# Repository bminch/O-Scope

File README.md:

# O-Scope
This repository contains the PCB design files, firmware, and software for the O-Scope, which is a low-cost (i.e., a cut-tape BoM cost of about $30 
as of fall 2020) two-channel oscilloscope / single-channel waveform generator up to a bandwidth of 200 kHz that fits into a solderless breadboard.  The oscilloscope's vertical resolution is 12 bits and each channel is sampled at 4 MS/s.  Each channel has a sample buffer of 1,500 points.  The 
oscilloscope probes are differential and have an equivalent input impedance of 1 MΩ || 15 pF with two input voltage ranges: ±10V and ±2V.  The 
waveform generator is capable of producing DC, sinusoidal, square, and triangle waves with an adjustable offset in the range of 0 - 5V. For an overview 
and demonstration of the O-Scope, see https://youtu.be/0cz0oYtfNsY.

I designed this instrument during the summer of 2020 based on a prior prototype, which I had made during the summers of 2016 and 2017, in order to support 
a remote / hybrid offering of ENGR 1125: Introduction to Sensors, Instrumentation, and Measurement at Olin College during the spring of 2021 in the midst 
of the COVID-19 pandemic.  During October and November 2020, I hand assembled and calibrated 90 O-Scopes at home, as shown in https://youtu.be/zYawotioLMc.  We used these instruments successfully during the spring 2021 and spring 2022 offerings of the course at Olin.

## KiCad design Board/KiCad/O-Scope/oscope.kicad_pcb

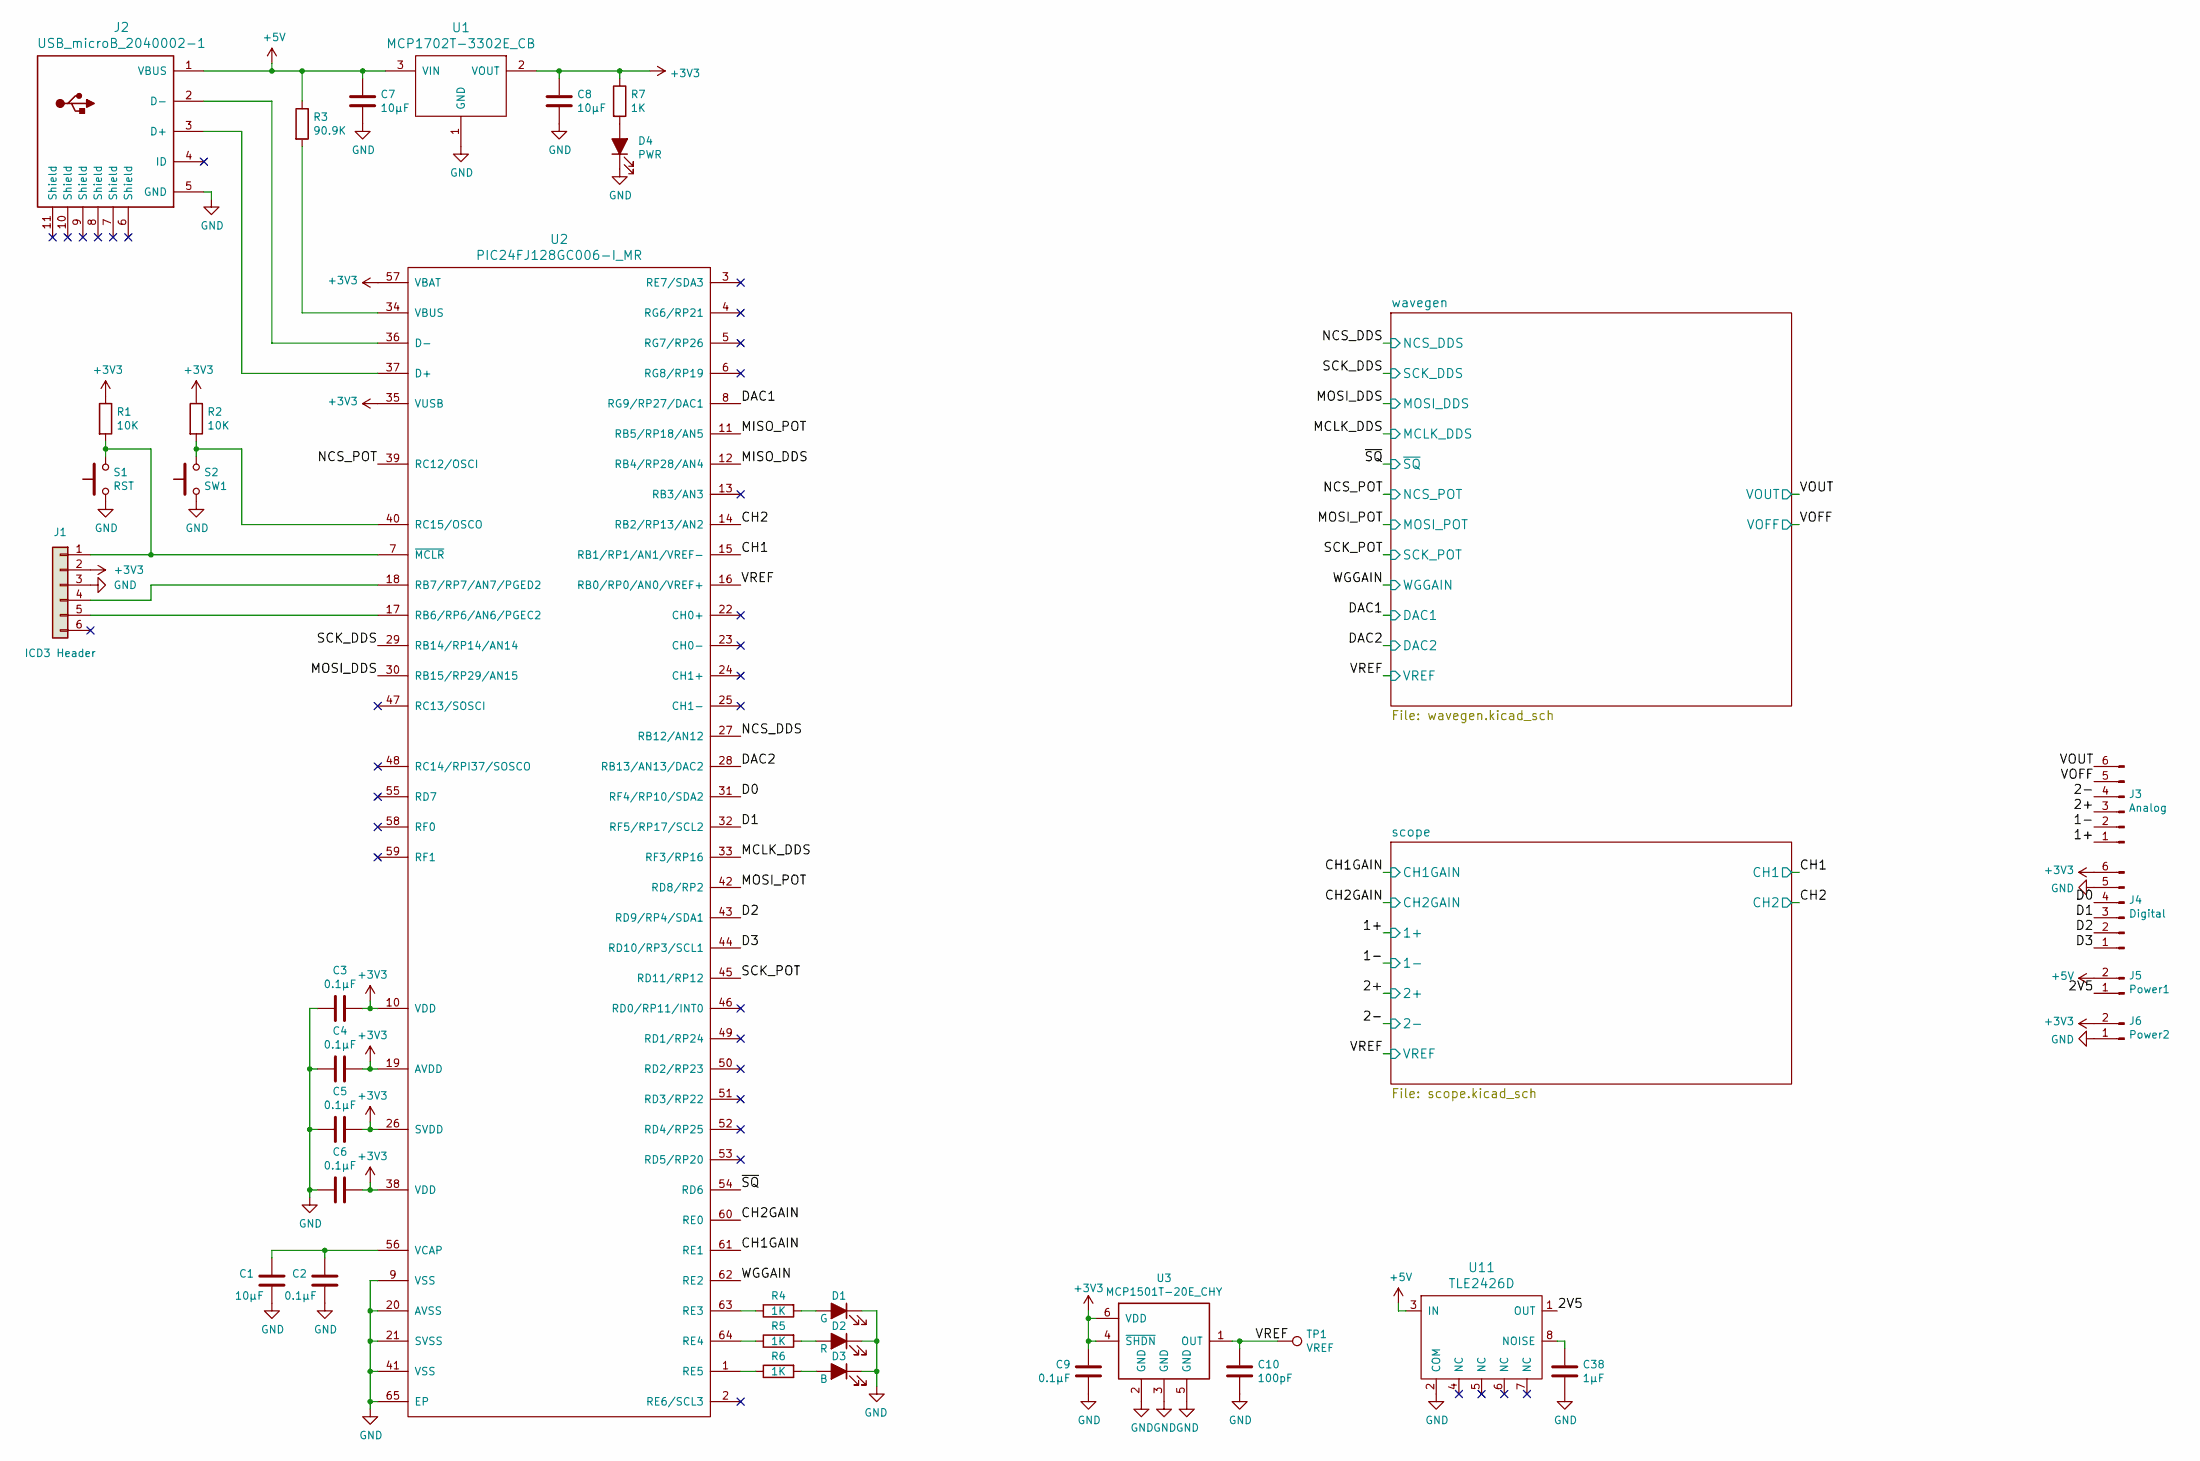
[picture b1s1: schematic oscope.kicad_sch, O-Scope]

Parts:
C1, C7, C8: 10µF; C_0805_2012Metric
C2, C3, C4, C5, C6, C9: 0.1µF; C_0603_1608Metric
C10: 100pF; C_0603_1608Metric
C38: 1µF; C_0603_1608Metric
D1: G; LED_0805_2012Metric
D2: R; LED_0805_2012Metric
D3: B; LED_0805_2012Metric
D4: PWR; LED_0805_2012Metric
J1: ICD3 Header; ICD3_header
J2: USB_microB_2040002-1
J3: Analog; PinHeader_1x06_P2.54mm_Vertical
J4: Digital; PinHeader_1x06_P2.54mm_Vertical
J5: Power1; PinHeader_1x02_P2.54mm_Vertical
J6: Power2; PinHeader_1x02_P2.54mm_Vertical
R1, R2: 10K; R_0603_1608Metric
R3: 90.9K; R_0603_1608Metric
R4, R5, R6, R7: 1K; R_0603_1608Metric
S1: RST; SW_SPST_B3U-1000P
S2: SW1; SW_SPST_B3U-1000P
TP1: VREF; 60mil_testpoint
U1: MCP1702T-3302E_CB; SOT-23
U2: PIC24FJ128GC006-I_MR; pic24fj128gc006
U3: MCP1501T-20E_CHY; SOT-23-6
U11: TLE2426D; SO-8_3.9x4.9mm_P1.27mm

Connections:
+3V3: C3.2, C4.2, C5.2, C6.2, C8.1, C9.1, J1.2, J4.6, J6.2, R1.1, R2.1, R7.1, U1.2 (VOUT), U2.10 (VDD), U2.19 (AVDD), U2.26 (SVDD), U2.35 (VUSB), U2.38 (VDD), U2.57 (VBAT), U3.4 (~SHDN), U3.6 (VDD); also elsewhere on the board
+5V: C7.1, J2.1 (VBUS), J5.2, R3.1, U1.3 (VIN), U11.3 (IN); also elsewhere on the board
/1+: J3.1; also elsewhere on the board
/1-: J3.2; also elsewhere on the board
/2+: J3.3; also elsewhere on the board
/2-: J3.4; also elsewhere on the board
/2V5: J5.1, U11.1 (OUT)
/CH1: U2.15 (RB1/RP1/AN1/VREF-); also elsewhere on the board
/CH1GAIN: U2.61 (RE1); also elsewhere on the board
/CH2: U2.14 (RB2/RP13/AN2); also elsewhere on the board
/CH2GAIN: U2.60 (RE0); also elsewhere on the board
/D0: J4.4, U2.31 (RF4/RP10/SDA2)
/D1: J4.3, U2.32 (RF5/RP17/SCL2)
/D2: J4.2, U2.43 (RD9/RP4/SDA1)
/D3: J4.1, U2.44 (RD10/RP3/SCL1)
/DAC1: U2.8 (RG9/RP27/DAC1); also elsewhere on the board
/DAC2: U2.28 (RB13/AN13/DAC2); also elsewhere on the board
/MCLK_DDS: U2.33 (RF3/RP16); also elsewhere on the board
/MISO_DDS: U2.12 (RB4/RP28/AN4)
/MISO_POT: U2.11 (RB5/RP18/AN5)
/MOSI_DDS: U2.30 (RB15/RP29/AN15); also elsewhere on the board
/MOSI_POT: U2.42 (RD8/RP2); also elsewhere on the board
/NCS_DDS: U2.27 (RB12/AN12); also elsewhere on the board
/NCS_POT: U2.39 (RC12/OSCI); also elsewhere on the board
/SCK_DDS: U2.29 (RB14/RP14/AN14); also elsewhere on the board
/SCK_POT: U2.45 (RD11/RP12); also elsewhere on the board
/VOFF: J3.5; also elsewhere on the board
/VOUT: J3.6; also elsewhere on the board
/VREF: C10.1, TP1.1, U2.16 (RB0/RP0/AN0/VREF+), U3.1 (OUT); also elsewhere on the board
/WGGAIN: U2.62 (RE2); also elsewhere on the board
/~SQ: U2.54 (RD6); also elsewhere on the board
GND: C1.1, C2.1, C3.1, C4.1, C5.1, C6.1, C7.2, C8.2, C9.2, C10.2, C38.2, D1.1 (K), D2.1 (K), D3.1 (K), D4.1 (K), J1.3, J2.5 (GND), J4.5, J6.1, S1.1, S2.1, U1.1 (GND), U2.9 (VSS), U2.20 (AVSS), U2.21 (SVSS), U2.41 (VSS), U2.65 (EP), U3.2 (GND), U3.3 (GND), U3.5 (GND), U11.2 (COM); also elsewhere on the board
unnamed: C1.2, C2.2, U2.56 (VCAP)
unnamed: C38.1, U11.8 (NOISE)
unnamed: D1.2 (A), R4.2
unnamed: D2.2 (A), R5.2
unnamed: D3.2 (A), R6.2
unnamed: D4.2 (A), R7.2
unnamed: J1.1, R1.2, S1.2, U2.7 (~MCLR)
unnamed: J1.4, U2.18 (RB7/RP7/AN7/PGED2)
unnamed: J1.5, U2.17 (RB6/RP6/AN6/PGEC2)
unnamed: J2.2 (D-), U2.36 (D-)
unnamed: J2.3 (D+), U2.37 (D+)
unnamed: R2.2, S2.2, U2.40 (RC15/OSCO)
unnamed: R3.2, U2.34 (VBUS)
unnamed: R4.1, U2.63 (RE3)
unnamed: R5.1, U2.64 (RE4)
unnamed: R6.1, U2.1 (RE5)

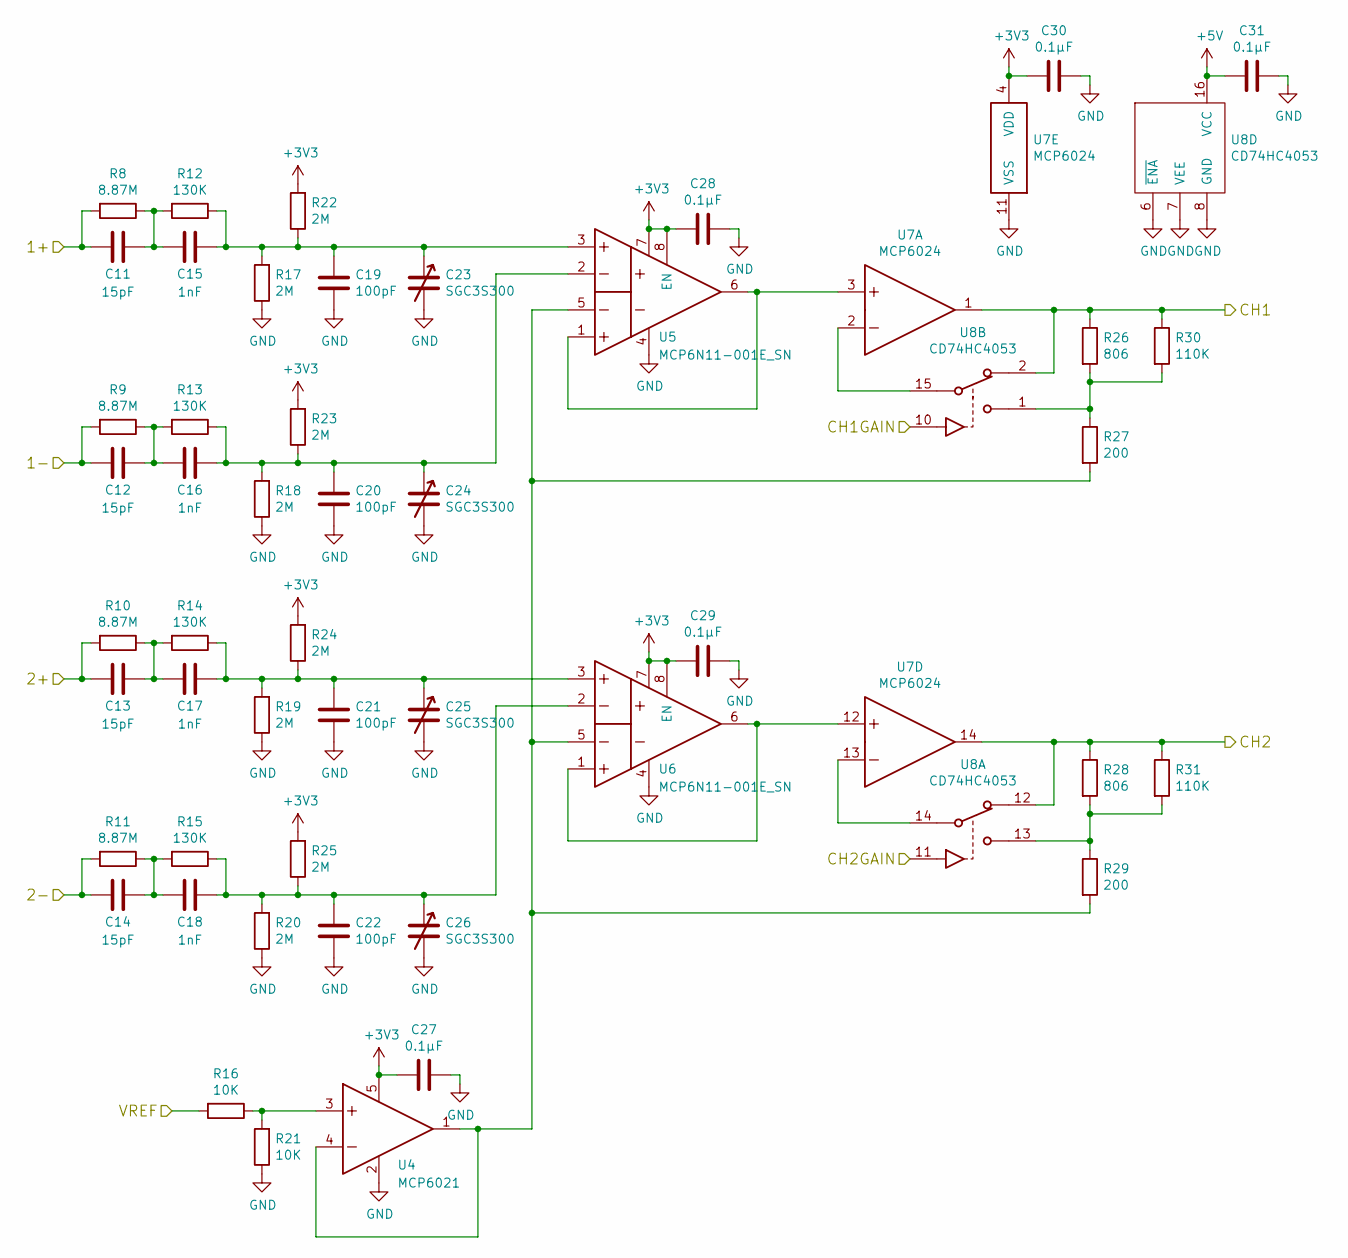
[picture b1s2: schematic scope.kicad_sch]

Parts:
C11, C12, C13, C14: 15pF; C_0603_1608Metric
C15, C16, C17, C18: 1nF; C_0603_1608Metric
C19, C20, C21, C22: 100pF; C_0603_1608Metric
C23, C24, C25, C26: SGC3S300; C_Trimmer_Sprague-Goodman_SGC3
C27, C28, C29, C30, C31: 0.1µF; C_0603_1608Metric
R8, R9, R10, R11: 8.87M; R_0805_2012Metric
R12, R13, R14, R15: 130K; R_0603_1608Metric
R16, R21: 10K; R_0603_1608Metric
R17, R18, R19, R20, R22, R23, R24, R25: 2M; R_0603_1608Metric
R26, R28: 806; R_0603_1608Metric
R27, R29: 200; R_0603_1608Metric
R30, R31: 110K; R_0603_1608Metric
U4: MCP6021; SOT-23-5
U5, U6: MCP6N11-001E_SN; SOIC-8_3.9x4.9mm_P1.27mm
U7: MCP6024; TSSOP-14_4.4x5mm_P0.65mm
U8: CD74HC4053; TSSOP-16_4.4x5mm_P0.65mm

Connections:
+3V3: C27.2, C28.2, C29.2, C30.2, R22.2, R23.2, R24.2, R25.2, U4.5, U5.7, U5.8 (EN), U6.7, U6.8 (EN), U7.4 (VDD); also elsewhere on the board
+5V: C31.2, U8.16 (VCC); also elsewhere on the board
/1+: C11.1, R8.2; also elsewhere on the board
/1-: C12.1, R9.2; also elsewhere on the board
/2+: C13.1, R10.2; also elsewhere on the board
/2-: C14.1, R11.2; also elsewhere on the board
/CH1: R26.1, R30.1, U7.1, U8.2; also elsewhere on the board
/CH1GAIN: U8.10; also elsewhere on the board
/CH2: R28.1, R31.1, U7.14, U8.12; also elsewhere on the board
/CH2GAIN: U8.11; also elsewhere on the board
/VREF: R16.2; also elsewhere on the board
GND: C19.2, C20.2, C21.2, C22.2, C23.2, C24.2, C25.2, C26.2, C27.1, C28.1, C29.1, C30.1, C31.1, R17.1, R18.1, R19.1, R20.1, R21.1, U4.2, U5.4, U6.4, U7.11 (VSS), U8.6 (~ENA), U8.7 (VEE), U8.8 (GND); also elsewhere on the board
unnamed: C11.2, C15.1, R8.1, R12.2
unnamed: C12.2, C16.1, R9.1, R13.2
unnamed: C13.2, C17.1, R10.1, R14.2
unnamed: C14.2, C18.1, R11.1, R15.2
unnamed: C15.2, C19.1, C23.1, R12.1, R17.2, R22.1, U5.3
unnamed: C16.2, C20.1, C24.1, R13.1, R18.2, R23.1, U5.2
unnamed: C17.2, C21.1, C25.1, R14.1, R19.2, R24.1, U6.3
unnamed: C18.2, C22.1, C26.1, R15.1, R20.2, R25.1, U6.2
unnamed: R16.1, R21.2, U4.3
unnamed: R26.2, R27.1, R30.2, U8.1
unnamed: R27.2, R29.2, U4.1, U4.4, U5.5, U6.5
unnamed: R28.2, R29.1, R31.2, U8.13
unnamed: U5.1, U5.6, U7.3
unnamed: U6.1, U6.6, U7.12
unnamed: U7.2, U8.15
unnamed: U7.13, U8.14

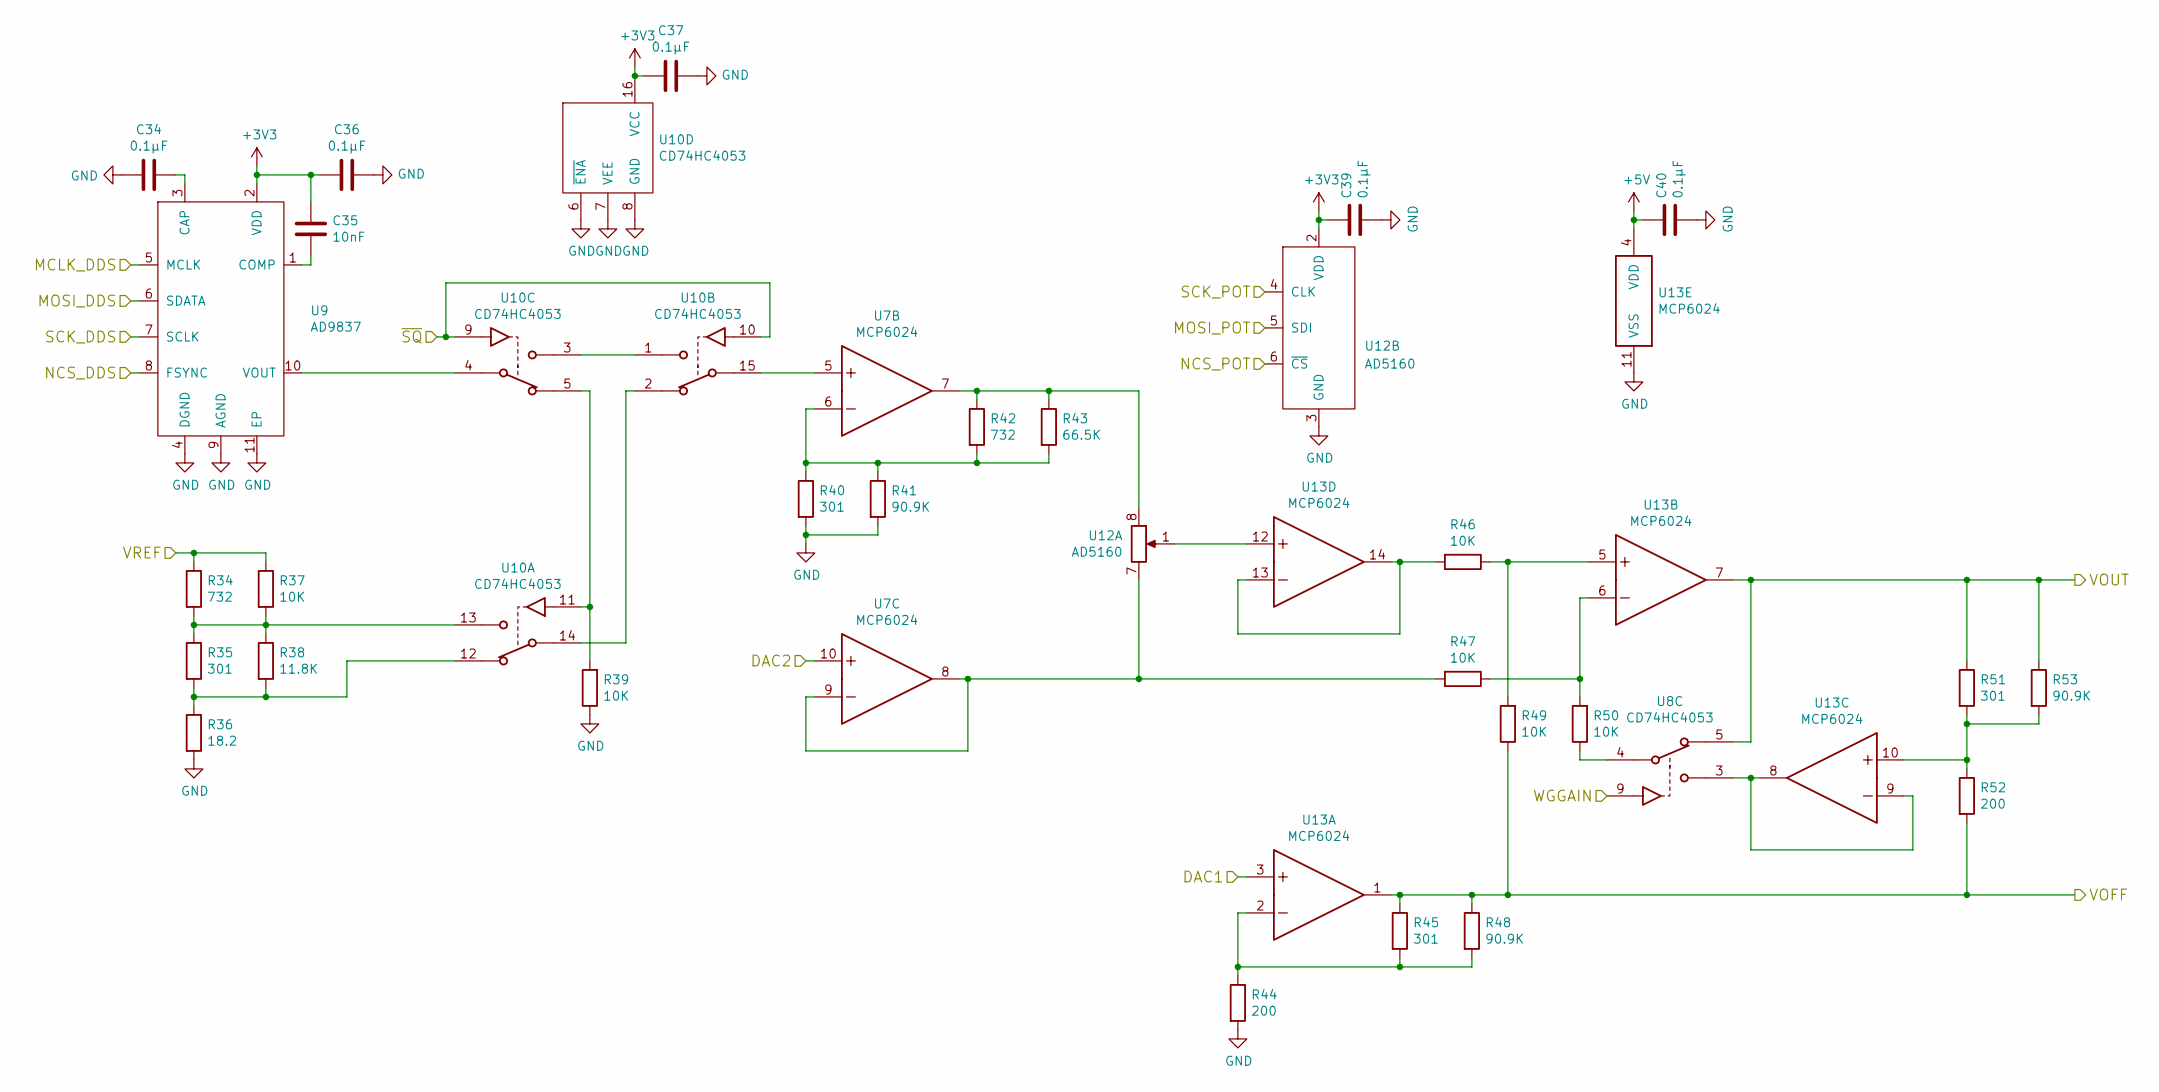
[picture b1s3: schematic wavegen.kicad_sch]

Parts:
C34, C36, C37, C39, C40: 0.1µF; C_0603_1608Metric
C35: 10nF; C_0603_1608Metric
R34, R42: 732; R_0603_1608Metric
R35, R40, R45, R51: 301; R_0603_1608Metric
R36: 18.2; R_0603_1608Metric
R37, R39, R46, R47, R49, R50: 10K; R_0603_1608Metric
R38: 11.8K; R_0603_1608Metric
R41, R48, R53: 90.9K; R_0603_1608Metric
R43: 66.5K; R_0603_1608Metric
R44, R52: 200; R_0603_1608Metric
U7, U13: MCP6024; TSSOP-14_4.4x5mm_P0.65mm
U8, U10: CD74HC4053; TSSOP-16_4.4x5mm_P0.65mm
U9: AD9837
U12: AD5160; TSOT-23-8

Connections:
+3V3: C35.1, C36.2, C37.2, C39.1, U9.2 (VDD), U10.16 (VCC), U12.2 (VDD); also elsewhere on the board
+5V: C40.1, U13.4 (VDD); also elsewhere on the board
/DAC1: U13.3; also elsewhere on the board
/DAC2: U7.10; also elsewhere on the board
/MCLK_DDS: U9.5 (MCLK); also elsewhere on the board
/MOSI_DDS: U9.6 (SDATA); also elsewhere on the board
/MOSI_POT: U12.5 (SDI); also elsewhere on the board
/NCS_DDS: U9.8 (FSYNC); also elsewhere on the board
/NCS_POT: U12.6 (~CS); also elsewhere on the board
/SCK_DDS: U9.7 (SCLK); also elsewhere on the board
/SCK_POT: U12.4 (CLK); also elsewhere on the board
/VOFF: R45.1, R48.1, R49.1, R52.2, U13.1; also elsewhere on the board
/VOUT: R51.1, R53.1, U8.5, U13.7; also elsewhere on the board
/VREF: R34.1, R37.1; also elsewhere on the board
/WGGAIN: U8.9; also elsewhere on the board
/~SQ: U10.9, U10.10; also elsewhere on the board
GND: C34.2, C36.1, C37.1, C39.2, C40.2, R36.2, R39.1, R40.2, R41.2, R44.2, U9.4 (DGND), U9.9 (AGND), U9.11 (EP), U10.6 (~ENA), U10.7 (VEE), U10.8 (GND), U12.3 (GND), U13.11 (VSS); also elsewhere on the board
unnamed: C34.1, U9.3 (CAP)
unnamed: C35.2, U9.1 (COMP)
unnamed: R34.2, R35.1, R37.2, R38.1, U10.13
unnamed: R35.2, R36.1, R38.2, U10.12
unnamed: R39.2, U10.5, U10.11
unnamed: R40.1, R41.1, R42.2, R43.2, U7.6
unnamed: R42.1, R43.1, U7.7, U12.8
unnamed: R44.1, R45.2, R48.2, U13.2
unnamed: R46.1, R49.2, U13.5
unnamed: R46.2, U13.13, U13.14
unnamed: R47.1, R50.2, U13.6
unnamed: R47.2, U7.8, U7.9, U12.7
unnamed: R50.1, U8.4
unnamed: R51.2, R52.1, R53.2, U13.10
unnamed: U10.1, U10.3
unnamed: U9.10 (VOUT), U10.4
unnamed: U10.2, U10.14
unnamed: U7.5, U10.15
unnamed: U12.1, U13.12
unnamed: U8.3, U13.8, U13.9

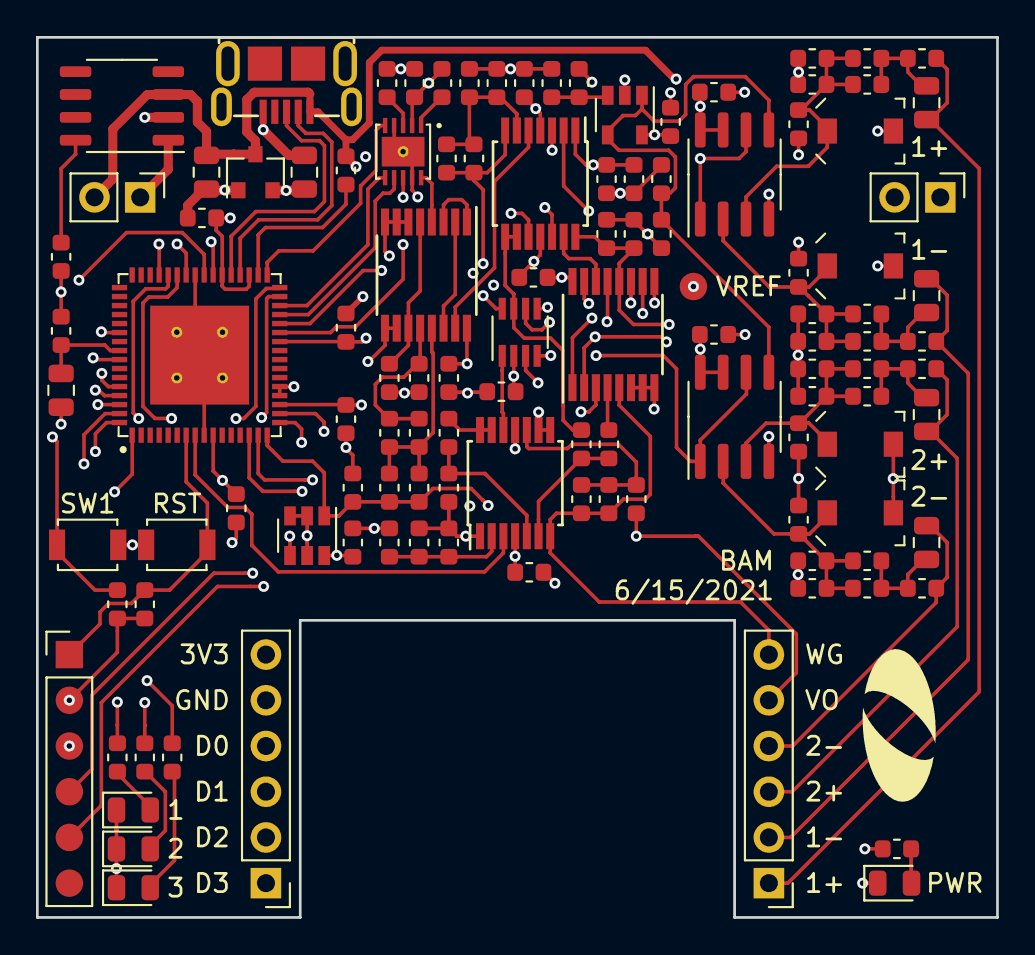
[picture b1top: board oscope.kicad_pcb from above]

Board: 4 copper layers, 53.3 x 48.9 mm, 117 parts (1 on the bottom side), 82 nets.

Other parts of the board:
OlinLogoLg1: G***; OlinLogoLg1
OlinLogoTruncated: G***; OlinLogoTruncated

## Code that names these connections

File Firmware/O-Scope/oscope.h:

#ifndef _OSCOPE_H_
#define _OSCOPE_H_

#include "pic24fj.h"
#include "common.h"
#include <stdint.h>

// LED pin definitions
#define LED1                LATEbits.LATE3
#define LED2                LATEbits.LATE4
#define LED3                LATEbits.LATE5

#define LED1_DIR            TRISEbits.TRISE3
#define LED2_DIR            TRISEbits.TRISE4
#define LED3_DIR            TRISEbits.TRISE5

// Tactile switch pin definitions
#define SW1                 PORTCbits.RC15

#define SW1_DIR             TRISCbits.TRISC15

// Digital header pin definitions
#define D0                  PORTFbits.RF4
#define D1                  PORTFbits.RF5
#define D2                  PORTDbits.RD9
#define D3                  PORTDbits.RD10

#define D0_DIR              TRISFbits.TRISF4
#define D1_DIR              TRISFbits.TRISF5
#define D2_DIR              TRISDbits.TRISD9
#define D3_DIR              TRISDbits.TRISD10

#define D0_LAT              LATFbits.LATF4
#define D1_LAT              LATFbits.LATF5
#define D2_LAT              LATDbits.LATD9
#define D3_LAT              LATDbits.LATD10

#define D0_RP               10
#define D1_RP               17
#define D2_RP               4
#define D3_RP               3

#define D0_OD               ODCFbits.ODF4
#define D1_OD               ODCFbits.ODF5
#define D2_OD               ODCDbits.ODD9
#define D3_OD               ODCDbits.ODD10

#define D0_PU               CNPU2bits.CN17PUE
#define D1_PU               CNPU2bits.CN18PUE
#define D2_PU               CNPU4bits.CN54PUE
#define D3_PU               CNPU4bits.CN55PUE

#define D0_PD               CNPD2bits.CN17PDE
#define D1_PD               CNPD2bits.CN18PDE
#define D2_PD               CNPD4bits.CN54PDE
#define D3_PD               CNPD4bits.CN55PDE

// AD9837 DDS interface pin defintions
#define nCS_DDS             LATBbits.LATB12
#define SCK_DDS             PORTBbits.RB14
#define MOSI_DDS            PORTBbits.RB15
#define MISO_DDS            PORTBbits.RB4
#define MCLK_DDS            PORTFbits.RF3

#define nCS_DDS_DIR         TRISBbits.TRISB12
#define SCK_DDS_DIR         TRISBbits.TRISB14
#define MOSI_DDS_DIR        TRISBbits.TRISB15
#define MISO_DDS_DIR        TRISBbits.TRISB4
#define MCLK_DDS_DIR        TRISFbits.TRISF3

#define SCK_DDS_RP          14
#define MOSI_DDS_RP         29
#define MISO_DDS_RP         28
#define MCLK_DDS_RP         16

// AD5160 digital potentiometer interface pin definitions
#define nCS_POT             LATCbits.LATC12
#define SCK_POT             PORTDbits.RD11
#define MOSI_POT            PORTDbits.RD8
#define MISO_POT            PORTBbits.RB5

#define nCS_POT_DIR         TRISCbits.TRISC12
#define SCK_POT_DIR         TRISDbits.TRISD11
#define MOSI_POT_DIR        TRISDbits.TRISD8
#define MISO_POT_DIR        TRISBbits.TRISB5

#define SCK_POT_RP          12
#define MOSI_POT_RP         2
#define MISO_POT_RP         18

// Wavegen mode pin defitions
#define nSQUARE             LATDbits.LATD6
#define WG_GAIN             LATEbits.LATE2

#define nSQUARE_DIR         TRISDbits.TRISD6
#define WG_GAIN_DIR         TRISEbits.TRISE2

// Scope channel gain pin definitions
#define CH1_GAIN            LATEbits.LATE1
#define CH2_GAIN            LATEbits.LATE0

#define CH1_GAIN_DIR        TRISEbits.TRISE1
#define CH2_GAIN_DIR        TRISEbits.TRISE0

// Peripheral remappable pin definitions
#define INT1_RP             1
#define INT2_RP             2
#define INT3_RP             3
#define INT4_RP             4

#define MOSI1_RP            7
#define SCK1OUT_RP          8
#define MOSI2_RP            10
#define SCK2OUT_RP          11

#define MISO1_RP            40
#define SCK1IN_RP           41
#define MISO2_RP            44
#define SCK2IN_RP           45

#define OC1_RP              18
#define OC2_RP              19
#define OC3_RP              20
#define OC4_RP              21
#define OC5_RP              22
#define OC6_RP              23
#define OC7_RP              24
#define OC8_RP              25
#define OC9_RP              35

#define U1TX_RP             3
#define U1RTS_RP            4
#define U2TX_RP             5
#define U2RTS_RP            6
#define U3TX_RP             28
#define U3RTS_RP            29
#define U4TX_RP             30
#define U4RTS_RP            31

#define U1RX_RP             36
#define U1CTS_RP            37
#define U2RX_RP             38
#define U2CTS_RP            39
#define U3RX_RP             35
#define U3CTS_RP            43
#define U4RX_RP             54
#define U4CTS_RP            55

// Convenience boolean values definitions
#define FALSE               0
#define TRUE                1

#define OFF                 0
#define ON                  1

#define OUT                 0
#define IN                  1

// Vendor request definitions
#define TOGGLE_LED1         0
#define TOGGLE_LED2         1
#define TOGGLE_LED3         2
#define READ_SW1            3
#define SET_DAC1            5
#define GET_DAC1            6
#define SET_DAC2            7
#define GET_DAC2            8
#define SET_DACS            9
#define GET_DACS            10
#define PULSE_MCP6N11_EN    11
#define TRIGGER             12
#define SET_PERIOD          13
#define GET_PERIOD          14
#define GET_SCOPE_BUFFER    15
#define GET_SWEEP_PROGRESS  16
#define SET_CH1_RANGE       17
#define GET_CH1_RANGE       18
#define SET_CH2_RANGE       19
#define GET_CH2_RANGE       20
#define SET_MAX_AVG         21
#define GET_MAX_AVG         22
#define GET_NUM_AVG         23
#define SET_WG_RANGE        24
#define GET_WG_RANGE        25
#define SET_NSQUARE         26
#define GET_NSQUARE         27
#define SPI_OUT_DDS         28
#define SPI_OUT_POT         29
#define SET_SHAPE_VAL       30
#define GET_SHAPE_VAL       31
#define SET_FREQ_VALS       32
#define GET_FREQ_VALS       33
#define SET_PHASE_VAL       34
#define GET_PHASE_VAL       35
#define SET_AMPLITUDE_VAL   36
#define GET_AMPLITUDE_VAL   37
#define SET_SQ_OFFSET_ADJ   38
#define GET_SQ_OFFSET_ADJ   39
#define SET_NSQ_OFFSET_ADJ  40
#define GET_NSQ_OFFSET_ADJ  41
#define READ_FLASH          42
#define WRITE_FLASH         43
#define ERASE_FLASH         44

void init_oscope(void);

#endif

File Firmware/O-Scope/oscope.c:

#include "oscope.h"
#include "scope.h"
#include "wavegen.h"

void init_oscope(void) {
    uint8_t *RPOR, *RPINR;
    uint16_t *ADTBL;
    uint16_t i;

    CLKDIV = 0x0100;        // RCDIV = 001 (4MHz, div2), 
                            // CPDIV = 00 (FOSC = 32MHz, FCY = 16MHz)

    OSCTUN = 0x9000;        // enable FRC self tuning with USB host clock

    // Configure digital pins to be outputs
    D0_DIR = OUT; D0 = 0;
    D1_DIR = OUT; D1 = 0;
    D2_DIR = OUT; D2 = 0;
    D3_DIR = OUT; D3 = 0;

    // Make all pins digital I/Os
    ANSB = 0;
    ANSC = 0;
    ANSD = 0;
    ANSF = 0;
    ANSG = 0;

    ANSBbits.ANSB0 = 1;         // configure RB0 (AN0) for analog function
    TRISBbits.TRISB0 = 1;       // tristate RB0's output driver

    ANSBbits.ANSB1 = 1;         // configure RB1 (AN1) for analog function
    TRISBbits.TRISB1 = 1;       // tristate RB0's output driver

    ANSBbits.ANSB2 = 1;         // configure RB2 (AN2) for analog function
    TRISBbits.TRISB2 = 1;       // tristate RB2's output driver

    ANSBbits.ANSB3 = 1;         // configure RB3 (AN3) for analog function
    TRISBbits.TRISB3 = 1;       // tristate RB3's output driver

    ANSGbits.ANSG9 = 1;         // configure RG9 (DAC1) for analog function
    TRISGbits.TRISG9 = 1;       // tristate RG9's output driver
    DAC1CON = 0x8081;           // enable DAC1, no trigger, and reference is DREF+

    ANSBbits.ANSB13 = 1;        // configure RB13 (DAC2) for analog function
    TRISBbits.TRISB13 = 1;      // tristate RB13's output driver
    DAC2CON = 0x8081;           // enable DAC2, no trigger, and reference is DREF+

    // Configure LED pins as outputs, set to low (off)
    LED1_DIR = OUT; LED1 = OFF;
    LED2_DIR = OUT; LED2 = OFF;
    LED3_DIR = OUT; LED3 = OFF;

    // Configure SW pins as inputs
    SW1_DIR = IN;

    // Configure channel gain pins
    CH1_GAIN_DIR = OUT; CH1_GAIN = 0;
    CH2_GAIN_DIR = OUT; CH2_GAIN = 0;

    set_sweep_in_progress(FALSE);
    set_samples_left(SCOPE_BUFFER_SIZE / 2);
    clear_scope_buffer();

    // Configure DMA module
    DMACON = 0x8000;            // enable DMA peripheral with fixed priority scheme
    DMAL = 0x0000;
    DMAH = 0x2000;

    DMASRC0 = (uint16_t)&ADRES0;
    DMADST0 = (uint16_t)&scope_buffer[0];
    DMACNT0 = SCOPE_BUFFER_SIZE / 2;
    DMAINT0 = 0x2F00;           // set DMA0 trigger to pipeline ADC:
                                //   CHSEL = 0b101111 (pipeline ADC)
    DMACH0 = 0x0215;            // enable DMA CH0 with 
                                //   RELOAD = 1, 
                                //   SAMODE = 0b00 (fixed), 
                                //   DAMODE = 0b01 (increment), 
                                //   TRMODE = 0b01 (repeated one-shot), and 
                                //   SIZE = 0 (word)

    DMASRC1 = (uint16_t)&ADRES1;
    DMADST1 = (uint16_t)&scope_buffer[SCOPE_BUFFER_SIZE / 2];
    DMACNT1 = SCOPE_BUFFER_SIZE / 2;
    DMAINT1 = 0x2F00;           // set DMA1 trigger to pipeline ADC:
                                //   CHSEL = 0b101111 (pipeline ADC)
    DMACH1 = 0x0215;            // enable DMA CH1 with 
                                //   RELOAD = 1, 
                                //   SAMODE = 0b00 (fixed), 
                                //   DAMODE = 0b01 (increment), 
                                //   TRMODE = 0b01 (repeated one-shot), and 
                                //   SIZE = 0 (word)

    IFS0bits.DMA1IF = 0;
    IEC0bits.DMA1IE = 1;

    set_max_avg(4);
    set_num_avg(0);

    // Configure pipelined ADC module
    ADCON1 = 0x0001;                // configure pipelined ADC module with
                                    //     FORM = 0000 (integer, raw data), 
                                    //     PUMPEN = 0 (charge pump disabled), 
                                    //     PWRLVL = 1 (full power, 1-10MHz clk)
    ADCON2 = 0x4700;                //     PVCFG = 01 (ADREF+ is ext VREF+),
                                    //     NVCFG = 0 (ADREF- is AVSS),
                                    //     BUFORG = 1 (buffer is indexed),
                                    //     ADPWR = 11 (ADC is always powered),
                                    //     BUFINT = 00 (no buffer interrupt),
                                    //     REFPUMP = 0 (ref chg pump disabled)
    ADCON3 = 0x0001;                //     ADRC = 0 (ADC clock from sys clock), 
                                    //     ADCS = 00000001 (TAD = 2*TSYS, 8MHz)

    ADL0CONH = 0xA040;              // configure sample list 0 with
                                    //     ASEN = 1 (auto-scan enabled),
                                    //     SLINT = 01 (int after auto-scan done),
                                    //     WM = 00 (all conversion results saved),
                                    //     CM = 000 (threshold matching disabled), 
                                    //     CTMEN = 0 (CTMU not used as Isrc),
                                    //     PINTRIS = 1 (IO pin high-Z during samp),
                                    //     MULCHEN = 0 (only one channel selected),
                                    //     SAMC = 00000 (TSAMP = 0.5*TAD)

    ADL0CONL = 0x0581;              //     SLENCLR = 0 (SLEN cleared by software), 
                                    //     SLTSRC = 00101 (trigger on Timer2), 
                                    //     THSRC = 1 (thresh comp from samp list thresh reg),
                                    //     SLSIZE = 00001 (samp list size = 2)

    ADL0PTR = 0;                    // sample list starts from first entry

    ADTBL = (uint16_t *)&ADTBL0;
    for (i = 0; i < 32; i++) {      // create sample list to alternate between AN1 (A1) and AN2 (A2)
        ADTBL[i++] = 1;
        ADTBL[i] = 2;
    }

    ADCON1bits.ADON = 1;            // enable ADC module
    while (ADSTATHbits.ADREADY == 0) {}     // wait until ADC module is ready

    ADCON1bits.ADCAL = 1;           // start ADC module calibration
    while (ADSTATHbits.ADREADY == 0) {}     // wait until ADC module is ready

    ADL0CONLbits.SAMP = 1;          // close sampling switch

    ADCON3bits.SLEN0 = 1;           // enable sample list 0 in ADCON3
    ADL0CONLbits.SLEN = 1;          // enable sample list 0

    set_period(15, 0);              // set Timer2 frequency to 1 MHz
//    set_period(159, 0);             // set Timer2 frequency to 100 kHz

    // Initialize the waveform generator
    init_wavegen();

    // Configure initial PWM frequencies to 1 kHz and duty cycles to 50%
    OC1RS = 15999;
    OC1R = 7999;
    OC1TMR = 0;

    OC2RS = 15999;
    OC2R = 7999;
    OC2TMR = 0;

    OC3RS = 15999;
    OC3R = 7999;
    OC3TMR = 0;

    OC4RS = 15999;
    OC4R = 7999;
    OC4TMR = 0;

    // Configure Timer1 to have a period of 20 ms
    T1CON = 0x0010;
    PR1 = 0x9C3F;

    TMR1 = 0;
    T1CONbits.TON = 1;
}

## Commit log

2022-12-23 Initial commit.
2023-01-24 Fixed scope probe input resistive divider values to match current O-Scopes (i.e. 1 MΩ input resistance instead of 10 MΩ).
